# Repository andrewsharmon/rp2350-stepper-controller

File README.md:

# RP2350 coordinated stepper controller

> **Work in progress.** Firmware runs on a Raspberry Pi Pico 2 bench setup.
> The custom board designs are an **unreviewed feasibility first pass**:
> schematics only, no PCB layout, not checked against datasheets or built.
> Don't fabricate them as-is.

A very low-cost, compact controller for up to **10 small stepper motors** (8 mm
micro steppers, 28BYJ-48 converted to bipolar, about 0.2 A per coil or less).
It's aimed at kinetic art first, then lab and robotics use.

There are no stepper-driver ICs. The RP2350 generates sine-PWM microstepping
itself (voltage mode), using PIO state machines fed by DMA, into cheap
DRV8833-class dual H-bridges (AT8833).

## Status

| # | Milestone | State |
|---|---|---|
| 1 | Hardware spec and KiCad schematics for all three boards | first pass, **not reviewed** (open part picks in [hardware/README.md](hardware/README.md)) |
| 2 | One motor: sine PWM via PIO + DMA | done, verified on hardware |
| 3 | 10-axis PWM, ADC monitor, e-stop/button ladder, WS2812 | done on Pico 2; ladder buttons not yet bench-wired |
| 4 | Trajectory generators and profiles, jog modes, telemetry | done (text telemetry; binary framing comes with milestone 5) |
| 5 | Coordinated groups and planner, USB protocol, host tool | done |
| 6 | I²C target, cam/LED shows, flash config, standalone mode | done; I²C target written for the RP2354B board but **untested** (no free pins or I²C master on the bench) |
| 7 | PCB layout, fab, bring-up of the board stack | |

What works today (measured on a Pico 2 + DRV8833 + 8 mm stepper):

- **PWM:** 20 kHz, four-segment H-bridge PWM with slow-decay brake off-time and 1/256-step sine microstepping. Duties below the driver's 0.5 µs minimum pulse are error-diffused.
- **10 axes:** each has its own position, velocity or jog mode on a 1 kHz trajectory tick. Drive amplitude depends on speed, with lower holding current at standstill. Core 1 is about 33-35% loaded, core 0 about 0.5%.
- **Coordinated groups:** up to 4 groups, each owning a set of axes. A group follows a queue of straight lines and arcs in joint space, with every axis starting and finishing together. Lookahead keeps it moving through gentle corners and chord-split arcs, and no axis exceeds its own limits. On the Pico 2, a 300-step-radius circle ran at a constant 800 steps/s and closed exactly.
- **Shows:** keyframe tracks for axes and LED pixels on one timeline, written as JSON, compiled and uploaded to one of 4 flash slots. Axes pass exactly through every keyframe (played as PVT), LED colours fade between keys, and shows can loop. A show is refused if any segment would exceed an axis's speed or acceleration limit. On the Pico 2, a looping 10-axis wave with 9 LED tracks hit all 360 keyframes checked exactly over 2.5 loops.
- **Built-in programs:** 12 looping motion patterns for a row of linear actuators (breathe, travel, standing, ripple, seesaw, zipper, domino, stairs, scan, chase, interference, drift), ±1000 full steps about position 0, all within the default limits (1500 steps/s, 2000 steps/s²). They run along the board's row of connectors, which on single_sh_proto is 5 6 7 8 9 10 1 2 3 4 from the far end to the USB end. They play through the show player as PVT streams, warming up from rest at their first pose. Position 0 is the power-up position, so power up with the actuators mid-stroke (or zero them there with `z`). `prog list`, `prog <n>`, `prog stop` on the console.
- **Standalone mode:** the buttons step through the built-in programs, then the stored shows, with no computer attached. Btn1 clears a latched stop once the e-stop is closed again, or starts / stops the selected entry; Btn2 selects the next one, switching to it if one is playing (the axes stop, then the new one starts). For 1.5 s after a press the axis LEDs show the entry's number as a bar: amber for programs 1-10, cyan for 11-12, magenta for shows. A boot program or show (`boot p<n>` / `boot <n>`, then `save`) starts at power-up.
- **Configuration in flash:** per-axis limits, motion profile, automatic amplitude curve (run low/high, hold, corner speeds) and wiring fixes (reverse direction, swap coils) survive power cycles. Two sectors are written alternately with a generation counter and CRC, so an interrupted save keeps the previous configuration.
- **Streamed PVT:** the host sends position/velocity/time points, and each axis follows a cubic through them. A 10-axis wave streamed at 20 ms per point tracked the ideal curve within 0.0005 steps. Running out of points while moving brakes safely.
- **Telemetry:** up to 1 kHz with selectable axes and fields (position, speed, mode, amplitude, PVT queue, plus motor voltage, ladder, stop state and the last applied command). Each line is numbered so a host can detect drops. Event lines report finished moves, PVT underruns and stops. At 1 kHz with every field on 10 axes, no lines were dropped and core 0 was 39% busy.
- **Electronic cams:** an axis can follow a cam table, so its position is a function of a leader's position: another axis, or one of two virtual leaders with their own speed ramps. Because it's position-based, followers retrace exactly when the leader reverses, at any speed. Cyclic tables can carry a net rise per cycle. Engaging blends in smoothly, and is refused if the follower couldn't keep up at the leader's limits. On the Pico 2, followers matched an independent evaluation of the cam within 0.0013 steps through forward and reverse runs. `save` also stores the loaded cam tables in flash; they are restored at boot.
- **Motion profiles per axis:** `trap`, `scurve` (the default: jerk-limited by a moving average, Tj = 30 ms), `smooth` (two moving averages), `cosine` and `quintic`. Every profile lands exactly on its target within the speed and acceleration limits, and moves can be redirected mid-move without jumps.
- **Safety:** an e-stop or driver fault on the analog ladder cuts all outputs in about 30 µs. A watchdog on core 0 drops outputs to coast if core 1 stalls.
- **Status LEDs:** a WS2812 chain shows overall status plus each axis's speed and direction.

How it works, from trajectory planning to PIO pin toggling: [docs/THEORY.md](docs/THEORY.md).

## Repository layout

```
tools/stepperctl/    host library + command line (binary protocol)
tools/shows/         example shows (JSON; format in tools/stepperctl/show.py)
tools/cams/          example cam tables (JSON: {"cyclic": true, "points": [[x, y], ...]})
tools/pvt_demo.py    host demo: streams a PVT wave over USB serial
tools/web/           browser pages (Web Serial, binary protocol): index.html actuators,
                     tof.html ToF sensor 3D viewer and settings
firmware/            Pico SDK (C) firmware
  third_party/tmf8829/  ams TMF8829 sensor application image (MIT)
  src/               motor PWM (PIO/DMA), microstepping, ADC monitor, ladder, LEDs
  boards/            board header for the custom RP2354B controller
  test/test_host.c   host-side tests (PWM encoder, microstep math, ladder, motion)
  tools/             sine table generator
hardware/            spec, KiCad schematics and BOMs (generated by hardware/gen)
```

## Building the firmware

Requirements:
- [Pico SDK](https://github.com/raspberrypi/pico-sdk) 2.1.1 (set `PICO_SDK_PATH`);
- an `arm-none-eabi` GCC toolchain;
- CMake and Ninja.

```bash
# Custom RP2354B controller (default board)
cmake -S firmware -B firmware/build -G Ninja
cmake --build firmware/build

# single_sh_proto prototype board
cmake -S firmware -B firmware/build-proto -G Ninja -DPICO_BOARD=single_sh_proto
cmake --build firmware/build-proto

# Raspberry Pi Pico 2 bench setup
cmake -S firmware -B firmware/build-pico2 -G Ninja -DPICO_BOARD=pico2
cmake --build firmware/build-pico2
```

Options: `-DNUM_MOTORS=1..10` (default 10), `-DLADDER_BYPASS=ON` (bench without
a ladder wired; never use with motors you can't stop by hand), `-DBOOT_TRACE=ON`.

Flash by copying `stepper.uf2` to the board in BOOTSEL mode, or with picotool:

```bash
picotool load -x firmware/build-pico2/stepper.uf2
```

Host tests (no hardware needed):

```bash
cd firmware/test
cc -std=c11 -O1 -Wall -Wextra -DCONFIG_HOST_TEST -I../src test_host.c ../src/hbridge_encode.c \
   ../src/microstep.c ../src/sine_lut.c ../src/ladder.c ../src/motion.c ../src/group.c \
   ../src/frame.c ../src/config.c ../src/show.c ../src/standalone.c ../src/cam.c ../src/cam_store.c \
   ../src/programs.c ../src/tof_frame.c ../src/tof_map.c -lm -o test_host && ./test_host
```

## ToF sensor (LightRanger 14 Click)

A MikroE LightRanger 14 Click (ams TMF8829 multi-zone dToF, 8x8 to 48x32 zones,
10 mm to 11 m) can hang off the Qwiic port. `tof on` makes I2C1 an I2C host for it
(the I2C target at 0x42 is off meanwhile; `tof off` gives the port back), downloads
the sensor's application into its RAM and loads the 8x8 preset. Driver:
`firmware/src/tmf8829.c`; service and frame streaming: `firmware/src/tof.c`.

Wiring: SDA, SCL, 3V3 and GND from the Qwiic connector. The Click must be set to
I2C, its EN pin (mikroBUS PWM) held high, and it needs 3V3 (bridge JP1
QWIIC_SUPPLY, or power it separately). INT isn't needed: the firmware polls.

`tools/web/tof.html` (Chrome or Edge, opened from file://) connects over USB
serial, switches the sensor on, picks the resolution preset, edits every
register of the configuration page, and draws each measurement as a 3D point
cloud (patches, dots or a surface) and a depth map, with PLY/CSV export. Demo
plays a synthetic scene without a board. From a terminal:

```
tof on            tof res 16         tof period 100     tof start
tof ?             tof get            tof set 0x53 10    tof stop / tof off
```

Not yet run against a real sensor: the register sequences follow ams's reference
driver, and the page was checked with its synthetic frames only.

### ToF map: the sensor drives the actuators

`tof map on` makes the row of linear actuators follow what the sensor sees in a
band across the middle of its field of view (the middle quarter of the rows, the
full width). The band is split left to right into one slice per axis, in the
board's row order (single_sh_proto's connectors run 5 6 7 8 9 10 1 2 3 4 from
the far end to the USB end), and each axis follows the nearest return in its
slice: 150 mm puts it at +1000 full
steps, 300 mm at -1000, and nearer or farther clamps to the ends. A slice with
nothing in it reads as far. Each axis's distance is smoothed (100 ms), and a new
position move goes out when the target changes by 4 steps or more, so the axis's
own limits and profile shape the motion.

Starting switches the sensor on if needed, loads the 16x16 preset, and sets
10 k iterations (the preset's 586 k is for the full range) with a 20 ms period.
Then it measures with no output, unless a host or the console is already
streaming; `tools/web/tof.html` can keep watching. It stops on `tof map off`,
an e-stop, the sensor stopping or failing, a program, show or stress test
starting, or a button starting one. Position 0 is the power-up position, as
for the programs, so power up mid-stroke (or zero there with `z`). The fixed-time
profiles (`cosine`, `quintic`) restart a segment on every retarget; use `scurve`
(the default), `smooth` or `trap`.

```
tof map on            tof map off           tof map ?      (band in zones, live mm and targets)
tof map range 150 300                       tof map steps 1000 -1000    (swap to reverse)
tof map order 1,2,3,4,5,6,7,8,9,10        tof map order board   (axes left to right)
tof map axes 5        tof map mirror on     tof map band 25 100   (height %, width %)
tof map smooth 100    tof map deadband 4    tof map iter 10   tof map period 20   tof map res 16
```

Settings aren't saved to flash yet. On single_sh_proto with the LightRanger 14
and ten actuators it ran at 49 measurements a second (16x16, 10 k iterations,
20 ms), with about 70 of the 256 zones returning; axes under an object at
~210 mm moved to about +150 steps while the rest went to the far end.

## Pico 2 bench setup

| Pico 2 | Connects to |
|---|---|
| GP0-GP3 | motor 1: DRV8833 module AIN1, AIN2, BIN1, BIN2 (motors 2-5 on GP4-GP19) |
| GP20 | WS2812 chain data in (pixel 0 status, pixels 1-10 axes) |
| GP26 | ladder: 10k to 3V3, 20k to GND (idle); see [hardware/README.md](hardware/README.md) |
| GP28 | board ID (optional) |
| VBUS / GND | DRV8833 VM and GND; pull the module's sleep pin (EEP) high |

Motors 6-10 have no pins on the Pico 2, but their state machines and DMA still
run, so the full 10-axis load is exercised.

The USB serial console takes line commands (type `help`). Some examples:

```
m 1 500          move axis 1 to 500 full steps
mr * -100        move every axis back 100 steps
j 3 400          jog axis 3 at 400 steps/s (stops unless repeated within 300 ms)
lim 1 1200 4000  axis 1 limits: 1200 steps/s, 4000 steps/s^2
prof * quintic   minimum-jerk moves on every axis (axes must be at rest)
cam 1 cyclic 0,0 100,40 200,50   cam table 1 (leader x, follower y); +50 per 200-step cycle
vl 1 lim 150 150 virtual leader 1 limits; ce 3 1 v1 makes axis 3 follow cam 1 behind it
vl 1 vel 100     run the virtual leader (negative reverses; followers retrace)
g 1 1,2 800      group 1 = axes 1 and 2, path speed 800 steps/s
gl 1 400 400     group line to (400, 400); ga 1 -300 0 360: full circle around (-300, 0)
p 2 150 300 20   PVT point: axis 2 reaches 150 steps at 300 steps/s, 20 ms after the last
pgo 1,2          start axes 1 and 2 following their queued points on the same tick
t 100            100 telemetry lines/s (header line names the columns)
tf pos,vel,mode  per-axis telemetry fields; ta 1,2 picks axes, ts adds system fields
te on            event lines: E <tick> done <ax> <pos>, underrun, stop, clear
echo off         for scripts: no echo or prompt
drive 1 40 60 25 axis 1 amplitude: 40% at low speed, 60% at high speed, 25% holding
dir 2 rev        reverse axis 2 (coils 2 ba swaps its coils)
cfg / save       show the configuration / write it to flash (axes at rest)
?                status, loads and per-axis table
```

### Host tool (binary protocol)

The same USB port also speaks a framed binary protocol (COBS + CRC-16; the
message spec is [firmware/src/protocol.h](firmware/src/protocol.h)). Frames
and the text console coexist: binary frames are wrapped in 0x00 bytes, which
the console never sends. `tools/stepperctl` is a standard-library Python
client and command line:

```bash
python3 tools/stepperctl ping
python3 tools/stepperctl move 1,2 250 --wait
python3 tools/stepperctl group 1 create 1,2 --feed 800
python3 tools/stepperctl group 1 arc -200 0 360
python3 tools/stepperctl telem --hz 200 --axes 1,2 --seconds 5 > log.csv
python3 tools/stepperctl show upload tools/shows/wave.json --slot 2
python3 tools/stepperctl show run 2          # show list / show stop
python3 tools/stepperctl boot 2 && python3 tools/stepperctl save   # run show 2 at power-up
python3 tools/stepperctl cam load 1 tools/cams/rise_dwell.json
python3 tools/stepperctl cam engage 3 1 v1 && python3 tools/stepperctl vl 1 vel 100
```

```python
from stepperctl import Client          # run from tools/, or put tools/ on sys.path
with Client() as c:
    seq = c.move([1], 500)
    c.wait_settled([1], after=seq)
```

Command-line tool tests (no hardware needed):
`python3 -m unittest discover -s tools/stepperctl -p 'test_*.py' -t tools`

### Browser control page

[tools/web/index.html](tools/web/index.html) drives the actuators from Chrome
or Edge over Web Serial: open the file directly (file:// works) and click
Connect. Each axis gets a position slider (drag to move), hold-to-jog
buttons, →0, Zero and Stop, with live position, speed and amplitude; there
are also an all-axes row, STOP ALL (or Esc), clear stop, manual or automatic
amplitude, speed and acceleration limits, the 12 built-in programs, and the
text console. It speaks the binary protocol on the same USB serial port, so
close any other program that has the port open first.

### I²C (Qwiic) — untested

On the RP2354B board the Qwiic port (I2C1, GPIO 46/47) is an I²C target at
address 0x42 carrying the same requests as the binary protocol, without COBS
framing: write `[type][payload…]`, then read `[n][type][reply payload…]`
(`n` = 0 means not ready yet, read again). See
[firmware/src/i2c_target.h](firmware/src/i2c_target.h). It is compiled out on
the Pico 2 bench build and has not been run on hardware yet.

`tools/pvt_demo.py` streams a travelling wave across every axis as PVT points
(standard-library Python, macOS/Linux):

```bash
tools/pvt_demo.py --amp 200 --hz 0.5 --seconds 15
```

## Notes

- **Sine table:** the SDK's float `sinf` returned wrong values near multiples
  of π/2 on the RP2350, which produced reverse pulses at each coil peak. The
  sine table is generated offline (`firmware/tools/gen_sine_lut.py`), and the
  motion code uses its own polynomials (`firmware/src/trig.h`).
- **Endless DMA:** on the RP2350, endless-mode DMA (`TRANS_COUNT` mode 0xF)
  still needs a non-zero count, or the channel completes immediately.

## License

[MIT](LICENSE), covering both firmware and hardware design files.

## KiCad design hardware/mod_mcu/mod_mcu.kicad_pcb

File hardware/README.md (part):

# Hardware specification

> **Status: unreviewed feasibility first pass.** These schematics, part picks
> and pin maps were put together quickly to check that the concept fits. They
> have not been reviewed, checked against datasheets, laid out or built.
> Expect errors; don't fabricate from them as-is.

Low-cost, compact, up-to-10-axis stepper controller for small high-resistance
steppers (8 mm micro steppers, 28BYJ-48 converted to bipolar, <= 0.2 A/coil).
The MCU generates sine PWM (voltage-mode microstepping) directly into cheap
dual H-bridges; there is no stepper-driver IC.

Prefer LCSC / JLCPCB "basic" parts wherever possible. Part picks marked TBD
are open.

## Stack overview

Three boards, 30 x 30 mm core, joined by fine-pitch board-to-board (BTB)
connectors at opposite edges. No screws: the enclosure captures the stack.

| Tier | Board | Layers | Size |
|---|---|---|---|
| 1 | Controller | 4, 1.0 mm thick | 30 x 30 mm |
| 2 | Universal driver | 2 | 30 x 30 mm |
| 3 | Connector / IO (variant-specific) | 2 | sized by connectors, may overhang |

## Tier 1 - Controller

- MCU: **RP2354B** (QFN-80, 48 GPIO, 2 MB in-package flash). Run the ARM cores (FPU).
- 12 MHz crystal, core-regulator inductor and decoupling per the RP2350 hardware design guide.
  - Crystal: Abracon ABM8-272-T3 (C20625731, 10 pF load, ESR <= 50 ohm). The guide's 15 pF / 1 k values are tuned for it; other crystals need retuning and testing.
  - Inductor: Abracon AOTA-B201610S3R3-101-T has a polarity dot. Lay it out in the same orientation as the Pico 2.
- USB-C receptacle with THT shell legs. The enclosure supports the receptacle so plug forces never reach the BTBs.
- CC1 / CC2: 5.1 k pull-downs, also routed to ADC (GPIO40/41) to read the source current advertisement.
- Power path: `VBUS -> PTC (~1.5 A hold, 1812) -> low-Vf Schottky -> V5_IN -> soft-start switch -> V5 bus -> BTB`.
- 3.3 V LDO (ME6211 class, <= 6 V input) fed from V5_IN, ahead of the switch.
- Soft-start: AO3401A P-FET (C15127) with 100 nF gate-source and 100 k gate-ground (tau 10 ms). At plug-in the cap holds the FET off, then it turns on over a few ms, so the ~70 uF on the V5 bus charges at about 0.1 A. USB sees only the ~11 uF on V5_IN at attach. External 5 V (tier 3) reaches V5_IN through the FET's body diode, then its channel.
- 2x Qwiic (JST-SH 4-pin) on I2C1:
  - The board is not powered from Qwiic. The ME6211 conducts from VOUT back to VIN, so a Qwiic-fed 3V3 would back-power the V5 bus (drivers, LEDs).
  - Solder jumpers for pull-ups (2.2-4.7 k) and for supplying 3V3 to downstream Qwiic devices.
- WS2812-class addressable LED on GPIO45. Its DOUT continues down the stack as LED_DATA.
  - Powered from V5 (needs >= 3.7 V). The 3.3 V data goes through a 74AHCT1G125 on V5 to meet VIH = 0.7 VDD.
- Buttons:
  - BOOTSEL (also readable at runtime), TS-1187A, right edge below connector B. The single boards use the TS-1088-AR02016 instead (same part as Btn1/Btn2).
  - Btn1 and Btn2 on the analog ladder (see below): XUNPU TS-1088-AR02016 (C720477, 3.9 x 3.0 mm, 2 pads), stacked in the top-right corner. They started over the BTB headers for rigidity, but their pads blocked the connector fan-out, so the case should support the board under them.
- SWD test pads.

## Tier 2 - Universal driver

- 10x **AT8833CQ** (Zhongkewei, LCSC C5120769, QFN-16 4 x 4).
  - DRV8833-compatible logic: 00 coast, 01 reverse, 10 forward, 11 brake.
  - VM 2.7-15 V, UVLO <= 2.5 V, 1.0 A RMS. Inputs have 100 k pull-downs.
  - Second source: JSMSEMI DRV8833RTYR / JSM8833RTYR (same QFN-16 4 x 4). Verify its pinout against TI DRV8833RTY before relying on it.
- Passives per chip:
  - AISEN / BISEN: 0.68-1 ohm to ground. Above I = 0.2 V / R (Vtrip 160-240 mV) the chip chops the current in slow decay; it does not report a fault. With 1 ohm that is 0.16-0.24 A. Give it a separate return to the star ground.
  - VCP: 0.1 uF to VM.
  - VINT: 1 uF.
  - These are the AT8833 datasheet values. TI's DRV8833 uses 0.01 uF and 2.2 uF, so don't copy from it.
  - VM: 1-2.2 uF ceramic at the pin.
- Shared bulk: 2-4x 10 uF 0805 spread over the V5 pour.
- nSLEEP: pulled high through 20-75 k (always awake, <= 3.5 mA idle per chip).
- nFAULT (open drain): wire-OR all chips onto the LADDER line.
- VMOTOR is the V5 bus directly.
- VMOTOR_SENSE: 1:5 divider to GPIO42.

AT8833CQ QFN-16 pinout: 1 AISEN, 2 AOUT2, 3 BOUT2, 4 BISEN, 5 BOUT1, 6 nFAULT,
7 BIN1, 8 BIN2, 9 VCP, 10 VM, 11 GND, 12 VINT, 13 AIN2, 14 AIN1, 15 nSLEEP,
16 AOUT1, plus the exposed pad to GND.

## Tier 3 - Connector / IO

- Motor connectors per variant. Each uses the motor's stock plug:
  - `io_xh`, 28BYJ-48: one JST-XH 5-pin (B5B-XH-A, C157991) per motor, ten total.
    - Pins: 1 blue, 2 pink, 3 yellow, 4 orange. Pin 5 (red centre tap) is not connected after the bipolar mod.
    - Coils: A = pins 1/3, B = pins 2/4.
  - `io_sh`, dual 8 mm micro steppers: one JST-SH 8-pin (BM08B-SRSS-TB, C160394) per motor pair, five total.
    - Pins 1-4 = first motor (A1 A2 B1 B2), pins 5-8 = second motor.
  - Firmware remaps coil order and polarity per axis, so lead-colour variations can be fixed in software.
- Optional external 5 V input -> Schottky -> V5 bus. This powers everything without USB.
- LED strip output (V5 / DATA / GND):
  - Data: 74AHCT1G125 buffer (powered from V5), then a 33-100 ohm series resistor.
  - Strip power, chosen by footprint: shared V5 through a polyfuse, or a separate LED power input.
- E-stop jack and panel buttons, in parallel with the ladder.
- Board ID: one resistor to GND, read through the controller pull-up on GPIO43. See the board-ID table below.

## Interconnect (BTB)

- **Part:** Hirose DF40, 0.4 mm pitch, 40 pins, **2.0 mm stack height**:
  - **Header** DF40C-40DP-0.4V(51) (C424643). Goes on the **underside of the upper board**. The header is the same for every DF40 stack height.
  - **Socket** DF40C(2.0)-40DS-0.4V(51) (C597934). Goes on the **top of the lower board**. The socket sets the stack height.
  - Rated 0.3 A per contact. The four corner contacts (pins 1, 2, 39, 40) are metal fittings per Hirose (catalogue note 3): they are soldered for strength but left unconnected, leaving 36 usable pins.
  - The 2.0 mm stack leaves room between boards for low parts (0402 passives, QFNs, SOT-23) on the facing sides. Keep anything taller than ~1 mm off them, and don't put a part opposite another one on the facing board if the two heights add up to more than ~1.7 mm.
- **Footprints** are in `lib/stack.pretty`, generated by `gen/footprints.py` from the DF40 catalogue's recommended layouts:
  - Socket: 0.20 x 0.70 pads (rows 2.38-3.78 mm across), plus the 1.5 mm layout-prohibited strip between the rows as a copper keepout.
  - Header: 0.23 x 0.66 pads (rows 2.05-3.37 mm across), plus 0.35 mm metal-fitting tabs 0.30-0.65 mm beyond each row end.
  - Pin 1 at -X. The socket's odd row is at -Y; the header's is drawn at +Y, so after the flip onto the underside header pin n sits over socket pin n. Still check it in the 3D viewer before ordering.
- **Not polarized** (Hirose note 5). Two connectors per interface at offset positions key the stack so the boards only mate one way: A is 2 mm below the board centre line, B on it.
- BTB pins carry roughly 0.3-0.5 A each.
- The authoritative pin lists are `btb_a()` and `btb_b()` in `gen/build.py`.

| Connector | Controller <-> driver | Driver <-> tier 3 |
|---|---|---|
| A | motors 1-7 inputs (28), 4x V5, 3x GND, 3V3, 4 corner NC | motors 1-7 outputs (28), 4x V5, 4x GND, 4 corner NC |
| B | motors 8-10 inputs (12), LED_DATA, LADDER, BOARD_ID, VMOT_SENSE, 9x V5, 11x GND, 4 corner NC | motors 8-10 outputs (12), LED_DATA, LADDER, BOARD_ID, 9x V5, 12x GND, 4 corner NC |

Pin order follows the MCU's pin order, so the controller's traces fan in without crossing. Connectors are placed pin 1 at the top: A down the left edge (power, then M1 from the MCU's top-left corner, M2-M5 down its left side, M6-M7 round its bottom-left), B down the right edge (utilities, then M10, M9, M8). M6/M7 are on A so they don't cross the crystal and SWD pins on the MCU's bottom side. The driver board shares V5 between both connectors, so the uneven V5 split doesn't matter. The driver's sockets copy the controller headers' positions and rotation.

**Board ID:** the 10 k 1% pull-up to 3V3 is on the controller. Each tier-3 variant fits one resistor to GND, 5% is fine. With no tier 3 attached, the line reads 3.3 V.

The values are common 0402 parts. Ranges are worst case for a 5% ID resistor and the 1% pull-up; adjacent levels stay at least 249 mV apart, and the thresholds sit midway between ranges.

| ID resistor | Nominal | Range (mV) | Threshold above (mV) | Board |
|---|---|---|---|---|
| 0 ohm | 0 mV | 0 | 150 | |
| 1 k | 300 mV | 284-316 | 440 | |
| 2.2 k | 595 mV | 566-624 | 820 | |
| 4.7 k | 1055 mV | 1012-1098 | 1350 | io_sh (dual 8 mm micro steppers) |
| 10 k | 1650 mV | 1599-1699 | 1960 | io_xh (28BYJ-48) |
| 22 k | 2269 mV | 2225-2310 | 2500 | |
| 47 k | 2721 mV | 2691-2749 | 3020 | |
| not fitted | 3300 mV | 3300 | - | no tier 3 attached |

## GPIO map (RP2354B)

| GPIO | Function |
|---|---|
| 0-39 | Motor n (1-10) on GPIO 4(n-1)..4(n-1)+3 = AIN1 AIN2 BIN1 BIN2 |
| 40 | USB-C CC1 (ADC0) |
| 41 | USB-C CC2 (ADC1) |
| 42 | VMOTOR_SENSE, 1:5 (ADC2). Can't tell external power from USB (both feed V5 through Schottkys) |
| 43 | Tier-3 board ID (ADC3) |
| 44 | Ladder (ADC4) |
| 45 | WS2812 data |
| 46 | Qwiic SDA (I2C1) |
| 47 | Qwiic SCL (I2C1) |

PIO allocation:

| PIO block | State machines | Use |
|---|---|---|
| PIO0 | SM0-3 | Motors 1-4 |
| PIO1 | SM0-3 | Motors 5-8 |
| PIO2 (GPIOBASE = 16) | SM0-1 | Motors 9-10 |
| PIO2 | SM2 | WS2812 |
| PIO2 | SM3 | Spare |

Use external pull-ups on all inputs on A2 silicon (RP2350-E9 erratum; fixed from A3).

## Ladder on GPIO44

```
3V3 --[10k]--+---------> GPIO44 (ADC4), 100 nF to GND
             |-- E-stop (NC) --[20k]-- GND   (solder jumper bypass when no e-stop)
             |-- Btn1 ---------[10k]-- GND
             |-- Btn2 ---------[3.3k]- GND
             '-- nFAULT (open drain, all drivers)
```

| Condition | Voltage | Meaning |
|---|---|---|
| E-stop open or cable cut | 3.3 V | STOP |
| Idle | ~2.2 V | normal |
| Btn1 | ~1.3 V | user 1 |
| Btn2 | ~0.7 V | user 2 |
| nFAULT | ~0 V | driver fault, STOP |

Use 1% resistors. Thresholds sit midway between the levels; debounce over 2-3 samples.

A held button hides an open e-stop (e-stop open + Btn1 = 1.65 V, + Btn2 = 0.82 V). Firmware latches a stop on 1.49-1.76 V held 5 ms, or on any button held over 3 s; see `firmware/src/ladder.h`.

## Electrical notes

- PWM frequency is about 20 kHz. The AT8833 input deglitch (about 450 ns) sets a minimum pulse of about 0.5 us, roughly 1% duty. Firmware dithers duties below that.
- Wait about 100 ms after power-up before energizing motors (V5 soft-start settling).
- USB budget comes from CC; brownout guard from VMOTOR_SENSE.
- RP2350-E9 (a GPIO with its input buffer on can sit near 2.2 V, which the AT8833's >= 2 V VIH reads as high) needs no hardware fix on the motor inputs. It is fixed in silicon from A3 (A4 is the production stepping; order A4). On A2 it can't occur after a power-on or RUN reset (input enable starts clear), and the firmware turns the motor pins' input buffers off (they are never read), so they stay off across a watchdog reset whether or not it resets the pads. The AT8833's 100 k pull-downs are enough.
- Tier 3: the NO_ESTOP jumper ships bridged. It must be cut when an e-stop is fitted, or the e-stop does nothing. Mark this on the silkscreen.

## Single board (`single_sh`)

Controller, driver and the `io_sh` connectors on one PCB, from the `single_sh/` schematic (`single()` in `gen/build.py`). Fully routed: 0 unconnected, no DRC errors, schematic parity clean.

- Schematic: a wired, hierarchical drawing (`gen/single_sh_sch.py`), unlike the label-only stack schematics.
  - Sheets: overview, power and USB, MCU, motor drivers, connectors and UI. Each block is framed, with design notes on its sheet.
  - Inter-sheet signals (motor lines, LADDER, BOARD_ID, I2C, CC, USB) are global labels. Power rails are power symbols, so their PCB nets are `GND`, `+3V3`, `V5` and so on; nets local to a sheet are named `/<sheet>/<label>`, e.g. `/Power/V5_IN`.
  - The AT8833 uses a project symbol (`lib/stack.kicad_sym`, written by `build.py`) with the DRV8833RTY pin numbers, laid out for the drawing; VINT is typed as an output, so it needs no PWR_FLAG.

- **122 x 20 mm**, 4 layers, 1.6 mm thick. All parts on top; only the THT legs of the USB-C and the JST-PH/XH connectors come through.
- Layers: F.Cu parts and signals, In1 solid GND, In2 V5, B.Cu signals. In2 has a 3V3 island under the MCU, joined to the LDO by a thin finger along the -y edge.
- Along the board: USB-C (mouth on the short edge) and power path | drivers M4 M3 M2 M1 | MCU | drivers M10 M9 M8 M7 M6 M5 | LED strip connector.
  - Motor connectors run along one long edge in the order J12 J11 | J15 J14 J13, so each motor bus leaves the MCU in pin order and never crosses itself.
  - Qwiic x2, BOOTSEL, e-stop, panel buttons, 5 V in, status LED and LED power run along the other long edge, above the drivers.
- Driver cell: AT8833 rotated so its outputs face the connector. VINT/VM/VCP caps sit above it; the 0603 sense resistors sit below, ISEN pads inboard, each GND pad with its own via (R16 and R20 instead tie to the neighbouring cell's GND pad).
  - BOUT2 runs down between the two ISEN pads and BOUT1 under R_B's body. The resistors went 0805 -> 0603 in place on the routed board: pad 1 (ISEN) kept, GND pad 0.275 mm inboard (R5 and R11 keep the GND pad instead, clear of a neighbouring via and track).
  - The connector's pin order (B2 B1 A2 A1, left to right) runs against the driver's (A1 A2 B2 B1), so A1/A2 hop over B1/B2 on short In2 jumpers (4 vias per motor).
  - Swapping this board's connector pin assignment (pins 1-2 = coil B, pins 3-4 = coil A reversed) would remove the jumpers, if firmware maps coil order and polarity per board. Not done, because the cable pinout would then differ from `io_sh`.
- V5 enters the In2 plane through via clusters at the soft-start FET, the external 5 V diode and the LED-strip fuse.
- Layout source: `single_sh()` in `gen/pcbgen.py` (placement and zones).
  - The driver cells and the core regulator were pre-routed by script. The rest was routed with Freerouting 2.5.0 plus a small grid router.
  - Those routing scripts are not in the repo; the board is hand-edited from here.
- Silkscreen: reference designators are hidden (too dense).
  - Motor numbers sit above each connector; function labels are on top where they fit, otherwise on the underside.
  - The underside also carries the NO_ESTOP cut warning.
  - The 4 remaining silkscreen warnings are outlines touching each other or the board edge.

### Fabrication (JLCPCB)

`gen/jlcfab.py` writes the order files to `single_sh/jlcpcb/`: Gerbers + Excellon drill (zipped), the BOM and the placement (CPL) file. Run it with KiCad's Python; `--check` also verifies the placements.

```bash
/Applications/KiCad/KiCad.app/Contents/Frameworks/Python.framework/Versions/Current/bin/python3 gen/jlcfab.py single_sh --check
```

- JLCPCB places each part with its own library footprint, so `CPL_FIX` corrects rotation and origin per LCSC part (SOT-23, SOT-23-5, WS2812, the JST connectors and USB-C need it).
  - `--check` fetches those footprints from the JLCEDA library and compares their pads with the KiCad pads.
  - All 142 placements land within 0.003 mm of centre with every pin on its own pad.
- Pin numbering traps:
  - SS54 (C22452): JLCPCB numbers 1 = anode, 2 = cathode, the reverse of KiCad's diodes. `PAD_MAP` handles it; the diodes need no extra rotation.
  - AOTA inductor (L1): the dot goes at the +1V1 end, as on the Pico 2 (RP2350 datasheet, regulator layout figure). JLCPCB's silkscreen and Abracon's top view put the dot at their pad 2, so pad 2 lands on +1V1. JLCPCB's placement preview shows the dot there; the order remark repeats it.
- The BOM has one line per LCSC part. JLCPCB unticks a part that appears on several lines.
- First order (2026-10-07, 10 boards, $314 before shipping):
  - PCB: 4 layers, 1.6 mm, ENIG (0.4 mm pitch QFN-80), min via 0.15/0.3 mm, plugged vias.
  - Assembly: Standard PCBA, top side, confirm parts placement with no auto-confirm.
- Cost drivers:
  - The 0.15 mm via option ($37) forces a 4-wire Kelvin test ($18) and TG155.
  - The WS2812B-2020 (D2) is Standard-PCBA only, as are its alternatives. Standard adds $25 setup, feeder fees and 5 mm edge rails (a 122 x 70 mm panel, nearly double the shipping weight). Economic with D2 left off was $265.
  - THT parts (JST PH/XH, the USB-C shell legs) are hand soldered, about $6.
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
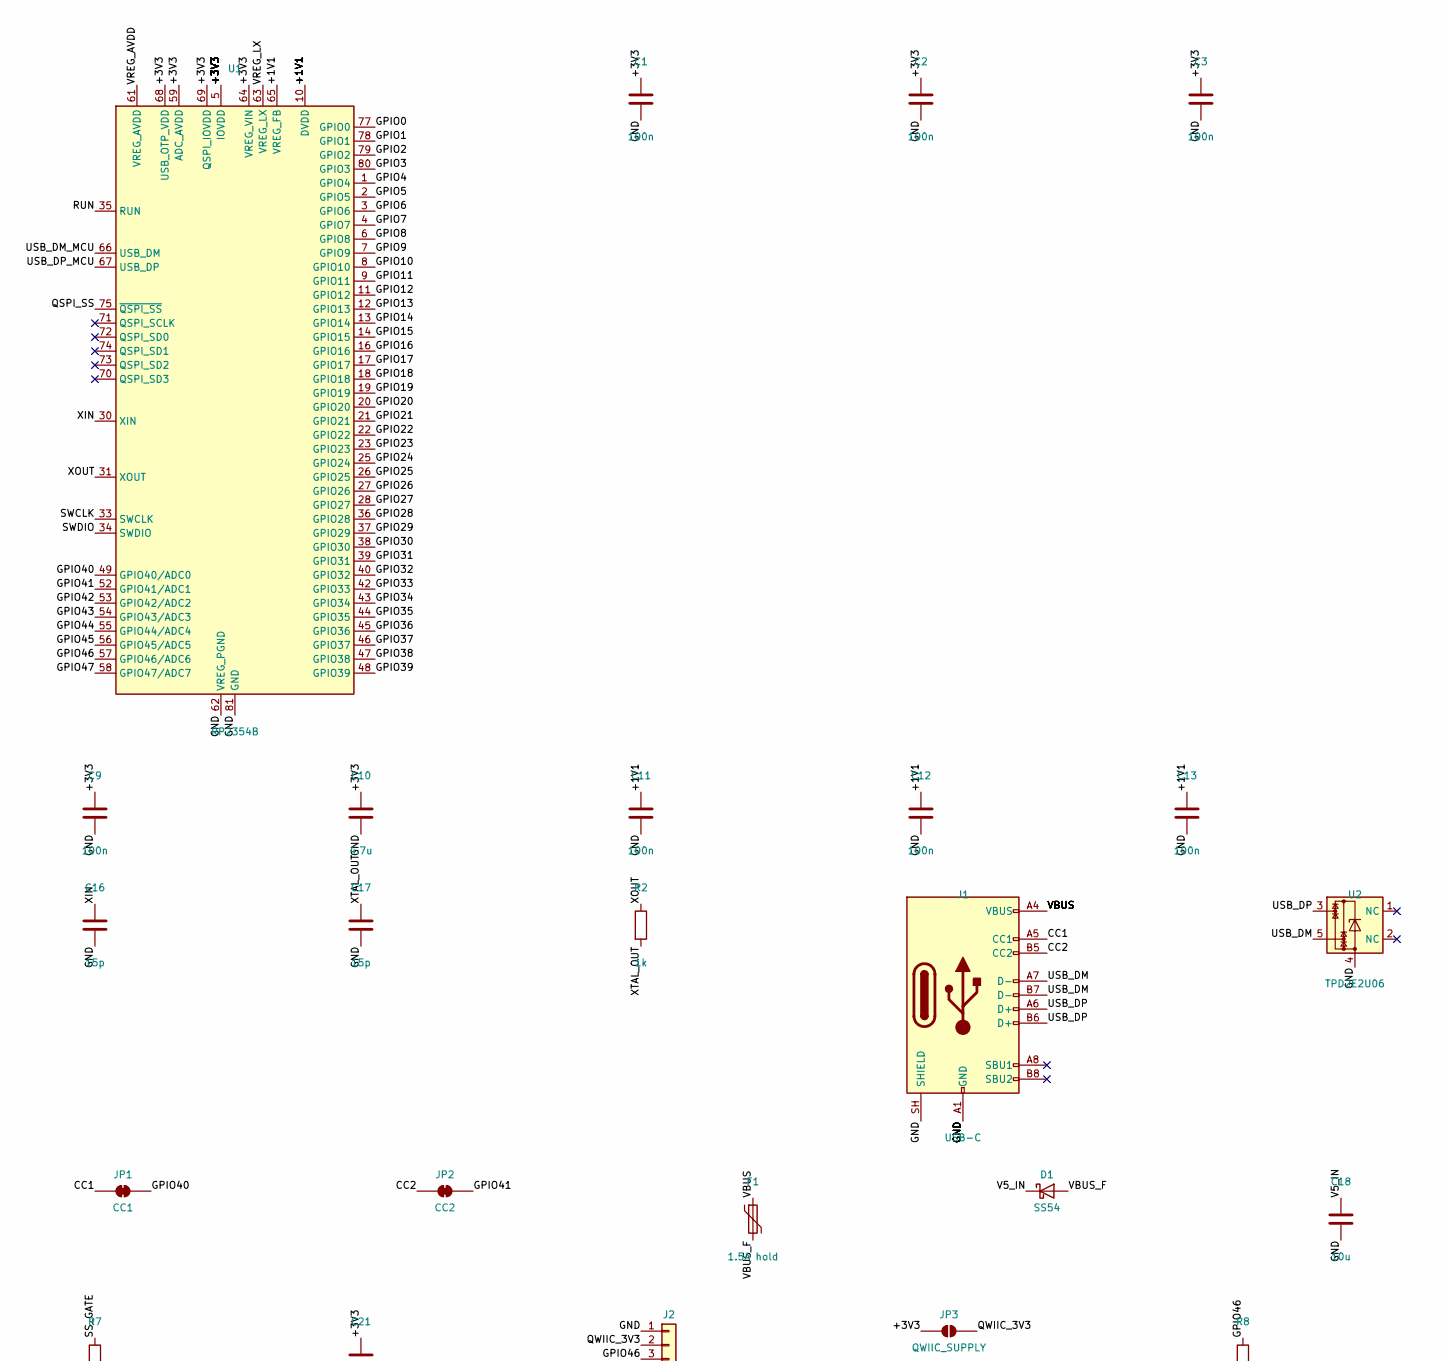
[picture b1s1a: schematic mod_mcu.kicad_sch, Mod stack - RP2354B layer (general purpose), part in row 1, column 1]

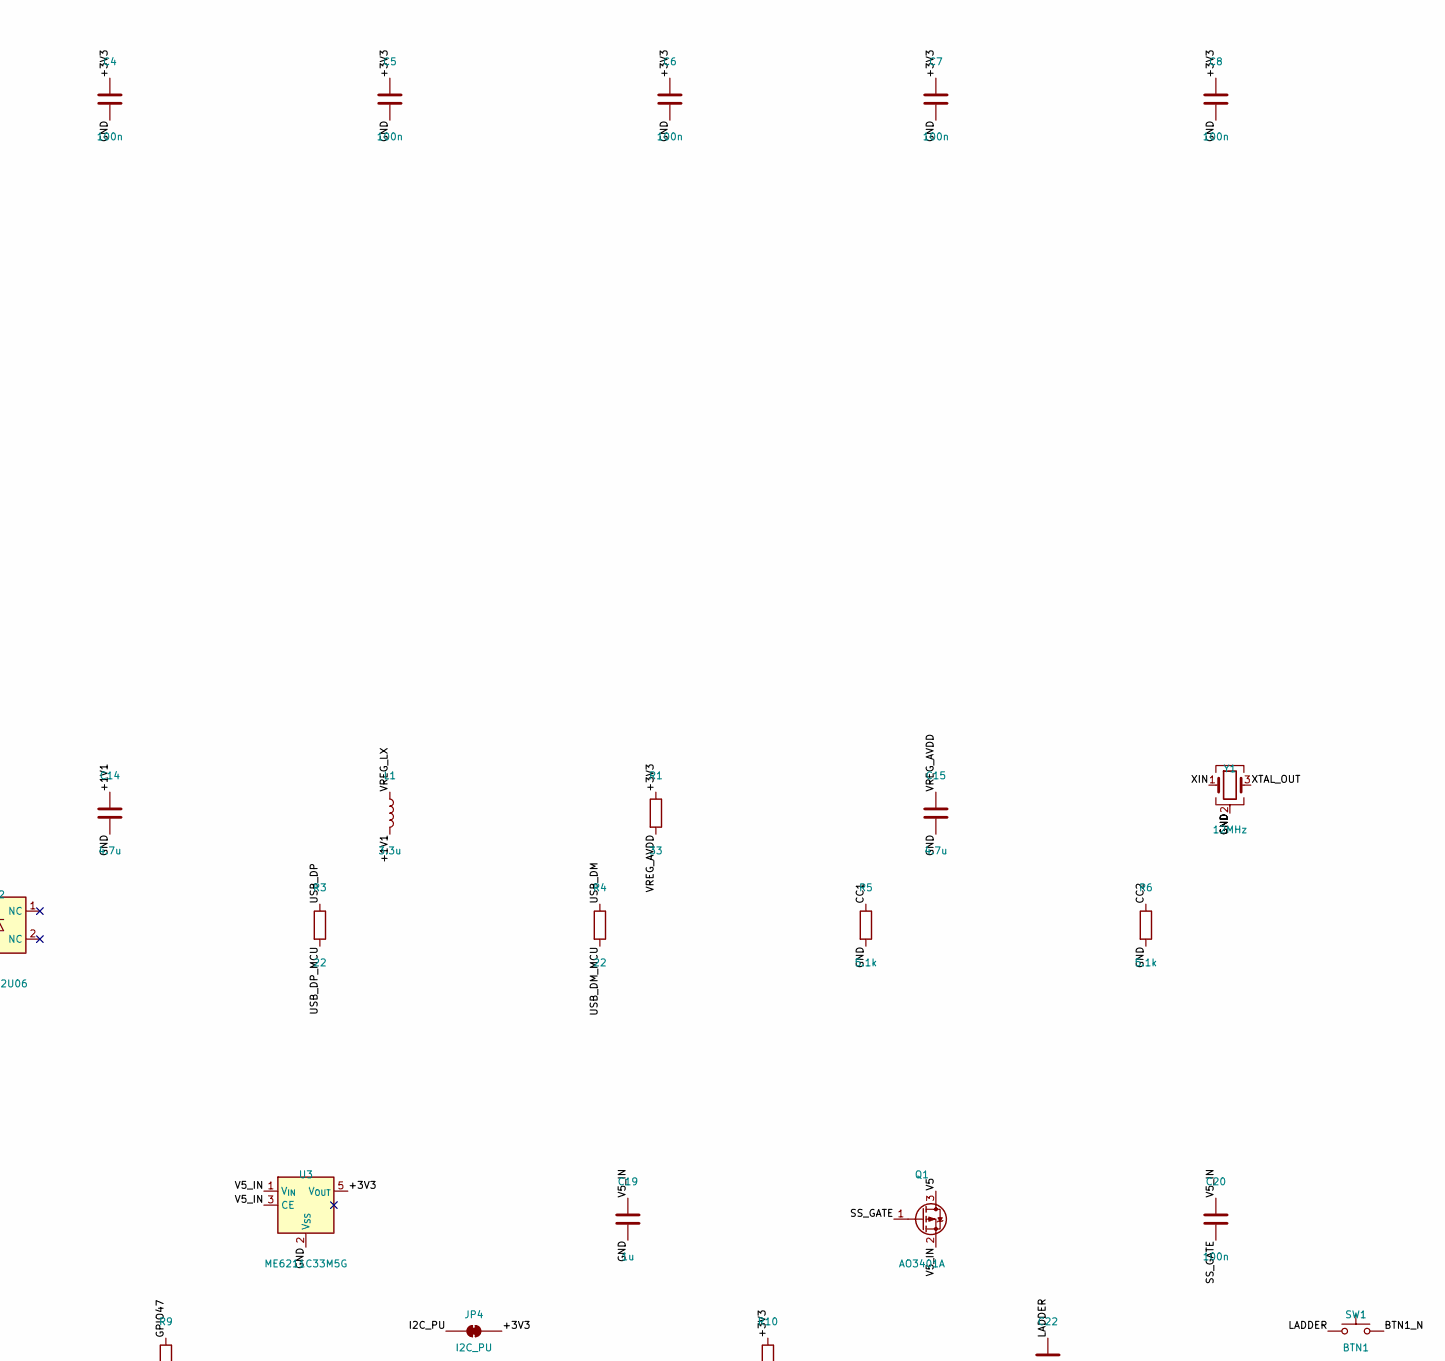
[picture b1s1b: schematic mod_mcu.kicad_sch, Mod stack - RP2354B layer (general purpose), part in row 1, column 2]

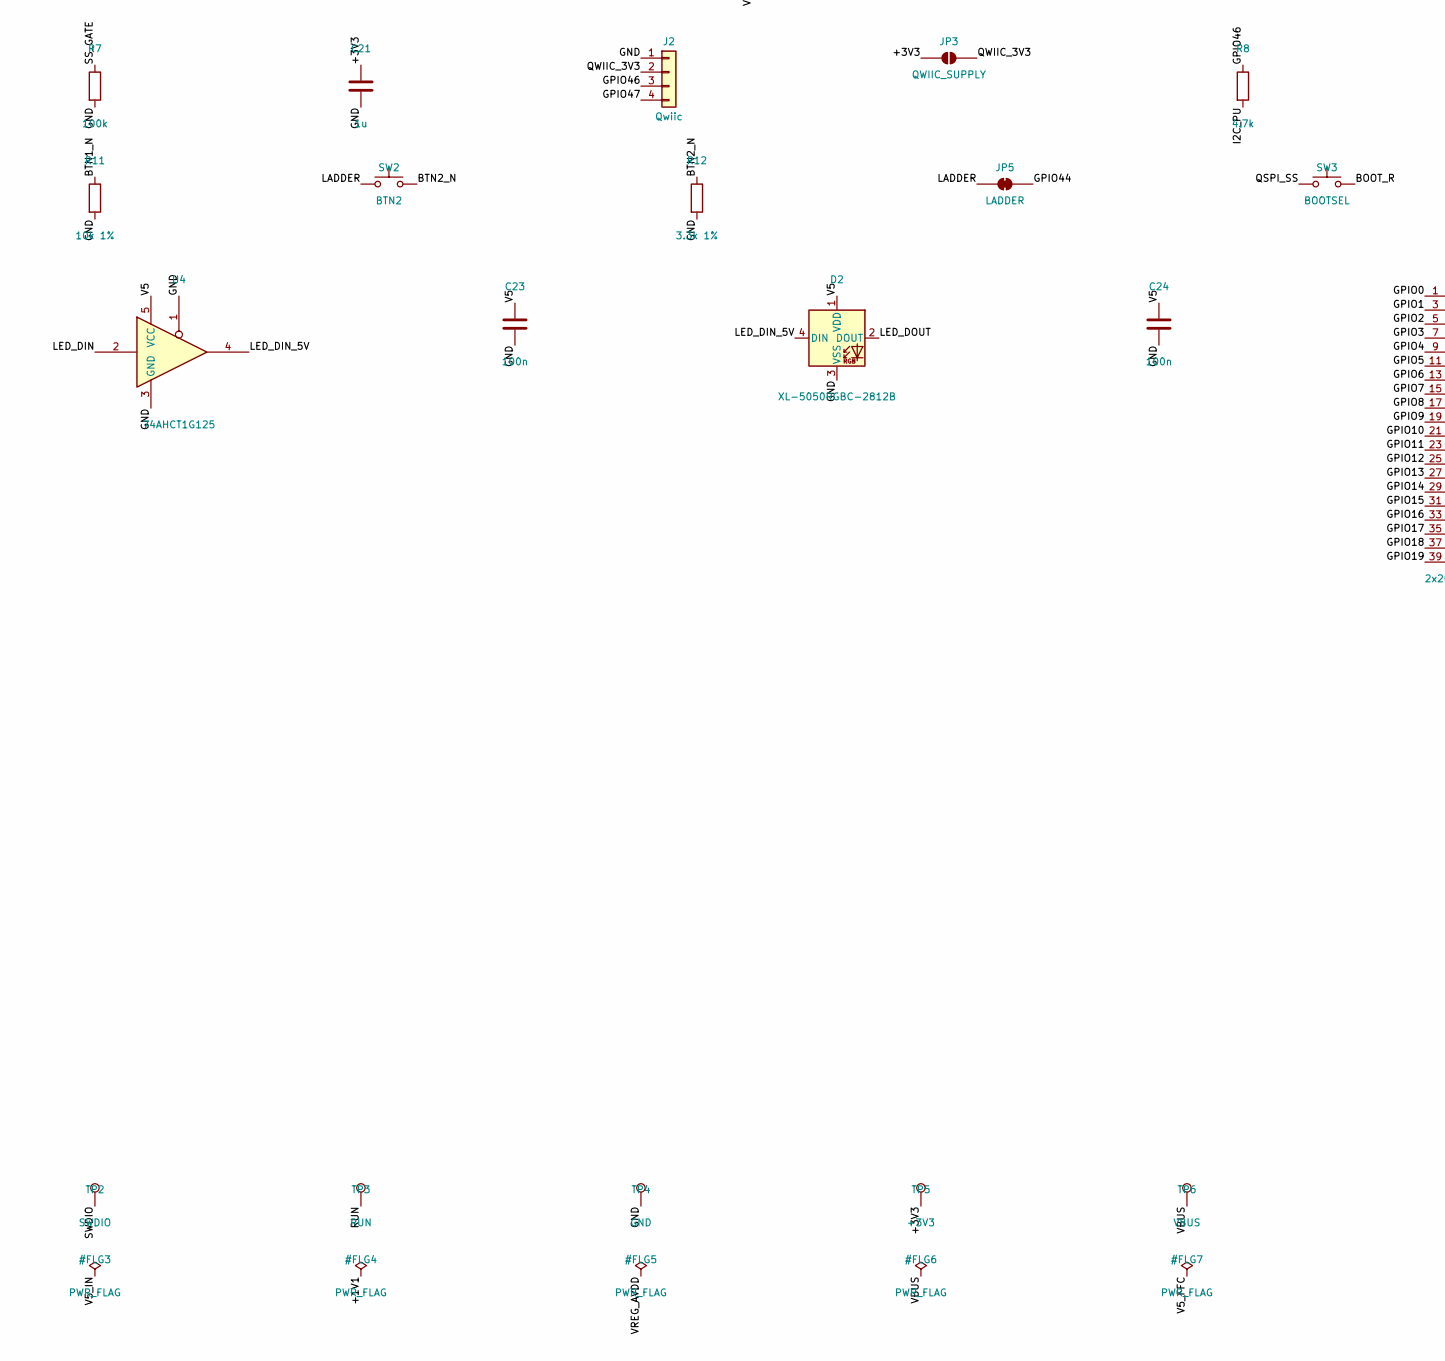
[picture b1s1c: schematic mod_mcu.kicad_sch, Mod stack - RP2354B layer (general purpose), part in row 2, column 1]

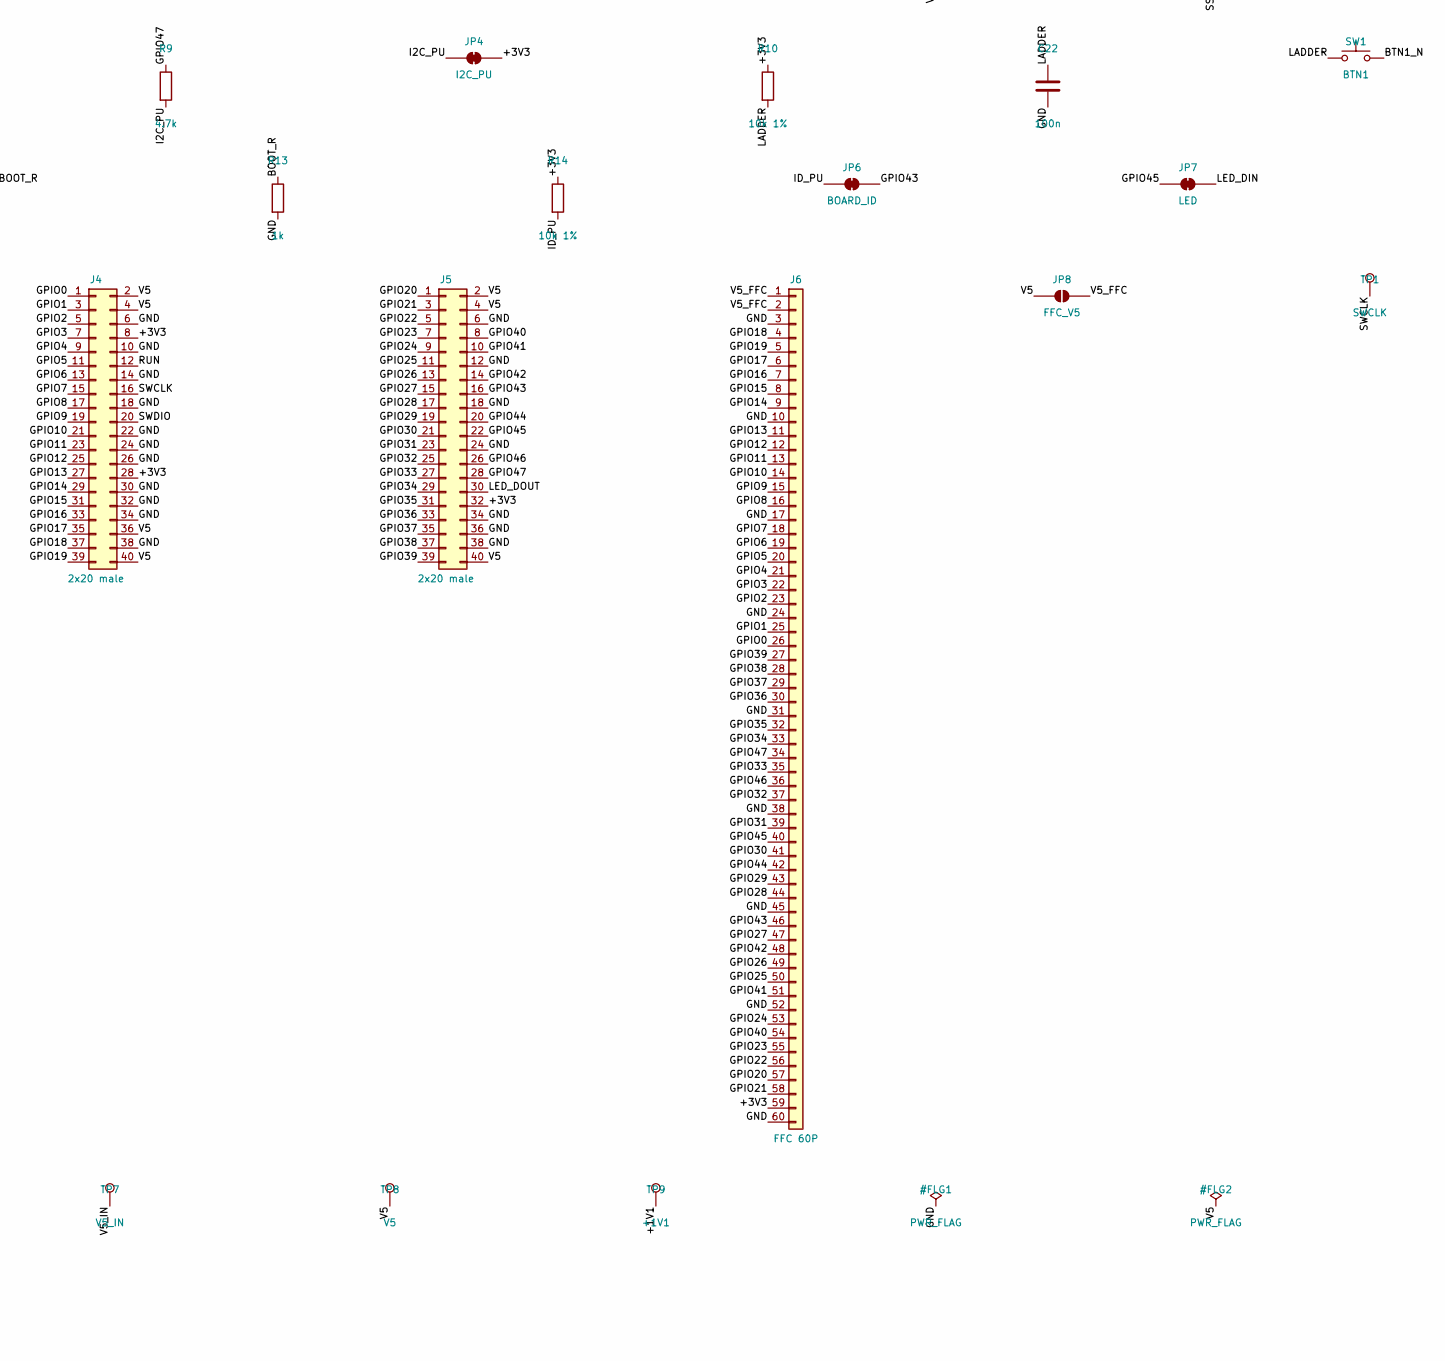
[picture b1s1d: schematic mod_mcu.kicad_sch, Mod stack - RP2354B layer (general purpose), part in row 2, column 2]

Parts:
C1, C2, C3, C4, C5, C6, C7, C8, C9, C11, C12, C13, C20, C22, C23, C24: 100n; C_0402_1005Metric; MPN CL05B104KO5NNNC; LCSC C1525
C10, C14, C15: 4.7u; C_0402_1005Metric; MPN CL05A475MP5NRNC; LCSC C23733
C16, C17: 15p; C_0402_1005Metric; MPN 0402CG150J500NT; LCSC C1548
C18: 10u; C_0603_1608Metric; MPN CL10A106KP8NNNC; LCSC C19702
C19, C21: 1u; C_0402_1005Metric; MPN CL05A105KA5NQNC; LCSC C52923
D1: SS54; D_SMA; MPN SS54; LCSC C22452
D2: XL-5050RGBC-2812B; LED_WS2812B_PLCC4_5.0x5.0mm_P3.2mm; MPN XL-5050RGBC-2812B; LCSC C2843785
F1: 1.5A hold; Fuse_1206_3216Metric; MPN SMD1206B150TFT; LCSC C269120
J1: USB-C; USB_C_Receptacle_HRO_TYPE-C-31-M-12; MPN TYPE-C-31-M-12; LCSC C165948
J2: Qwiic; JST_SH_BM04B-SRSS-TB_1x04-1MP_P1.00mm_Vertical; MPN BM04B-SRSS-TB; LCSC C160390
J4, J5: 2x20 male; PinHeader_2x20_P2.54mm_Vertical; MPN PZ254-2-20-Z-8.5; LCSC C3012260
J6: FFC 60P; FFC_0.5mm_60P_FlipTop; MPN 05A20L60P; LCSC C22435645
JP1: CC1; SolderJumper-2_P1.3mm_Bridged_RoundedPad1.0x1.5mm
JP2: CC2; SolderJumper-2_P1.3mm_Bridged_RoundedPad1.0x1.5mm
JP3: QWIIC_SUPPLY; SolderJumper-2_P1.3mm_Open_RoundedPad1.0x1.5mm
JP4: I2C_PU; SolderJumper-2_P1.3mm_Bridged_RoundedPad1.0x1.5mm
JP5: LADDER; SolderJumper-2_P1.3mm_Bridged_RoundedPad1.0x1.5mm
JP6: BOARD_ID; SolderJumper-2_P1.3mm_Bridged_RoundedPad1.0x1.5mm
JP7: LED; SolderJumper-2_P1.3mm_Bridged_RoundedPad1.0x1.5mm
JP8: FFC_V5; SolderJumper-2_P1.3mm_Open_RoundedPad1.0x1.5mm
L1: 3.3u; L_Cenker_CKCS201610; MPN AOTA-B201610S3R3-101-T; LCSC C42411119
Q1: AO3401A; SOT-23; MPN AO3401A; LCSC C15127
R1: 33; R_0402_1005Metric; MPN 0402WGF330JTCE; LCSC C25105
R2, R13: 1k; R_0402_1005Metric; MPN 0402WGF1001TCE; LCSC C11702
R3, R4: 22; R_0402_1005Metric; MPN 0402WGF220JTCE; LCSC C25092
R5, R6: 5.1k; R_0402_1005Metric; MPN 0402WGF5101TCE; LCSC C25905
R7: 100k; R_0402_1005Metric; MPN 0402WGF1003TCE; LCSC C25741
R8, R9: 4.7k; R_0402_1005Metric; MPN 0402WGF4701TCE; LCSC C25900
R10, R11, R14: 10k 1%; R_0402_1005Metric; MPN 0402WGF1002TCE; LCSC C25744
R12: 3.3k 1%; R_0402_1005Metric; MPN 0402WGF3301TCE; LCSC C25890
SW1: BTN1; SW_SPST_TS-1088-xR020; MPN TS-1088-AR02016; LCSC C720477
SW2: BTN2; SW_SPST_TS-1088-xR020; MPN TS-1088-AR02016; LCSC C720477
SW3: BOOTSEL; SW_SPST_TS-1088-xR020; MPN TS-1088-AR02016; LCSC C720477
TP1: SWCLK; TestPoint_Pad_D1.0mm
TP2: SWDIO; TestPoint_Pad_D1.0mm
TP3: RUN; TestPoint_Pad_D1.0mm
TP4: GND; TestPoint_Pad_D1.0mm
TP5: +3V3; TestPoint_Pad_D1.0mm
TP6: VBUS; TestPoint_Pad_D1.0mm
TP7: V5_IN; TestPoint_Pad_D1.0mm
TP8: V5; TestPoint_Pad_D1.0mm
TP9: +1V1; TestPoint_Pad_D1.0mm
U1: RP2354B; QFN-80-1EP_10x10mm_P0.4mm_EP3.4x3.4mm; MPN RP2354B; LCSC C39843328
U2: TPD2E2U06; SOT-553; MPN TPD2E2U06DRLR; LCSC C1972959
U3: ME6211C33M5G; SOT-23-5; MPN ME6211C33M5G-N; LCSC C82942
U4: 74AHCT1G125; SOT-23-5; MPN SN74AHCT1G125DBVR; LCSC C7484
Y1: 12MHz; Crystal_SMD_3225-4Pin_3.2x2.5mm; MPN ABM8-272-T3; LCSC C20625731

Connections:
/+1V1: C11.1, C12.1, C13.1, C14.1, L1.2, TP9.1, U1.10 (DVDD), U1.32 (DVDD), U1.51 (DVDD), U1.65 (VREG_FB)
/+3V3: C1.1, C2.1, C3.1, C4.1, C5.1, C6.1, C7.1, C8.1, C9.1, C10.1, C21.1, J4.8, J4.28, J5.32, J6.59, JP3.1 (A), JP4.2 (B), R1.1, R10.1, R14.1, TP5.1, U1.5 (IOVDD), U1.15 (IOVDD), U1.24 (IOVDD), U1.29 (IOVDD), U1.41 (IOVDD), U1.50 (IOVDD), U1.59 (ADC_AVDD), U1.60 (IOVDD), U1.64 (VREG_VIN), U1.68 (USB_OTP_VDD), U1.69 (QSPI_IOVDD), U1.76 (IOVDD), U3.5 (V_{OUT})
/BOOT_R: R13.1, SW3.2
/BTN1_N: R11.1, SW1.2
/BTN2_N: R12.1, SW2.2
/CC1: J1.A5 (CC1), JP1.1 (A), R5.1
/CC2: J1.B5 (CC2), JP2.1 (A), R6.1
/GND: C1.2, C2.2, C3.2, C4.2, C5.2, C6.2, C7.2, C8.2, C9.2, C10.2, C11.2, C12.2, C13.2, C14.2, C15.2, C16.2, C17.2, C18.2, C19.2, C21.2, C22.2, C23.2, C24.2, D2.3 (VSS), J1.A1 (GND), J1.A12 (GND), J1.B1 (GND), J1.B12 (GND), J1.SH (SHIELD), J2.1, J4.6, J4.10, J4.14, J4.18, J4.22, J4.24, J4.26, J4.30, J4.32, J4.34, J4.38, J5.6, J5.12, J5.18, J5.24, J5.34, J5.36, J5.38, J6.3, J6.10, J6.17, J6.24, J6.31, J6.38, J6.45, J6.52, J6.60, R5.2, R6.2, R7.2, R11.2, R12.2, R13.2, TP4.1, U1.62 (VREG_PGND), U1.81 (GND), U2.4, U3.2 (V_{SS}), U4.1, U4.3 (GND), Y1.2 (G), Y1.4 (G)
/GPIO0: J4.1, J6.26, U1.77 (GPIO0)
/GPIO1: J4.3, J6.25, U1.78 (GPIO1)
/GPIO2: J4.5, J6.23, U1.79 (GPIO2)
/GPIO3: J4.7, J6.22, U1.80 (GPIO3)
/GPIO4: J4.9, J6.21, U1.1 (GPIO4)
/GPIO5: J4.11, J6.20, U1.2 (GPIO5)
/GPIO6: J4.13, J6.19, U1.3 (GPIO6)
/GPIO7: J4.15, J6.18, U1.4 (GPIO7)
/GPIO8: J4.17, J6.16, U1.6 (GPIO8)
/GPIO9: J4.19, J6.15, U1.7 (GPIO9)
/GPIO10: J4.21, J6.14, U1.8 (GPIO10)
/GPIO11: J4.23, J6.13, U1.9 (GPIO11)
/GPIO12: J4.25, J6.12, U1.11 (GPIO12)
/GPIO13: J4.27, J6.11, U1.12 (GPIO13)
/GPIO14: J4.29, J6.9, U1.13 (GPIO14)
/GPIO15: J4.31, J6.8, U1.14 (GPIO15)
/GPIO16: J4.33, J6.7, U1.16 (GPIO16)
/GPIO17: J4.35, J6.6, U1.17 (GPIO17)
/GPIO18: J4.37, J6.4, U1.18 (GPIO18)
/GPIO19: J4.39, J6.5, U1.19 (GPIO19)
/GPIO20: J5.1, J6.57, U1.20 (GPIO20)
/GPIO21: J5.3, J6.58, U1.21 (GPIO21)
/GPIO22: J5.5, J6.56, U1.22 (GPIO22)
/GPIO23: J5.7, J6.55, U1.23 (GPIO23)
/GPIO24: J5.9, J6.53, U1.25 (GPIO24)
/GPIO25: J5.11, J6.50, U1.26 (GPIO25)
/GPIO26: J5.13, J6.49, U1.27 (GPIO26)
/GPIO27: J5.15, J6.47, U1.28 (GPIO27)
/GPIO28: J5.17, J6.44, U1.36 (GPIO28)
/GPIO29: J5.19, J6.43, U1.37 (GPIO29)
/GPIO30: J5.21, J6.41, U1.38 (GPIO30)
/GPIO31: J5.23, J6.39, U1.39 (GPIO31)
/GPIO32: J5.25, J6.37, U1.40 (GPIO32)
/GPIO33: J5.27, J6.35, U1.42 (GPIO33)
/GPIO34: J5.29, J6.33, U1.43 (GPIO34)
/GPIO35: J5.31, J6.32, U1.44 (GPIO35)
/GPIO36: J5.33, J6.30, U1.45 (GPIO36)
/GPIO37: J5.35, J6.29, U1.46 (GPIO37)
/GPIO38: J5.37, J6.28, U1.47 (GPIO38)
/GPIO39: J5.39, J6.27, U1.48 (GPIO39)
/GPIO40: J5.8, J6.54, JP1.2 (B), U1.49 (GPIO40/ADC0)
/GPIO41: J5.10, J6.51, JP2.2 (B), U1.52 (GPIO41/ADC1)
/GPIO42: J5.14, J6.48, U1.53 (GPIO42/ADC2)
/GPIO43: J5.16, J6.46, JP6.2 (B), U1.54 (GPIO43/ADC3)
/GPIO44: J5.20, J6.42, JP5.2 (B), U1.55 (GPIO44/ADC4)
/GPIO45: J5.22, J6.40, JP7.1 (A), U1.56 (GPIO45/ADC5)
/GPIO46: J2.3, J5.26, J6.36, R8.1, U1.57 (GPIO46/ADC6)
/GPIO47: J2.4, J5.28, J6.34, R9.1, U1.58 (GPIO47/ADC7)
/I2C_PU: JP4.1 (A), R8.2, R9.2
/ID_PU: JP6.1 (A), R14.2
/LADDER: C22.1, JP5.1 (A), R10.2, SW1.1, SW2.1
/LED_DIN: JP7.2 (B), U4.2
/LED_DIN_5V: D2.4 (DIN), U4.4
/LED_DOUT: D2.2 (DOUT), J5.30
/QSPI_SS: SW3.1, U1.75 (~QSPI_SS)
/QWIIC_3V3: J2.2, JP3.2 (B)
/RUN: J4.12, TP3.1, U1.35 (RUN)
/SS_GATE: C20.2, Q1.1 (G), R7.1
/SWCLK: J4.16, TP1.1, U1.33 (SWCLK)
/SWDIO: J4.20, TP2.1, U1.34 (SWDIO)
/USB_DM: J1.A7 (D-), J1.B7 (D-), R4.1, U2.5
/USB_DM_MCU: R4.2, U1.66 (USB_DM)
/USB_DP: J1.A6 (D+), J1.B6 (D+), R3.1, U2.3
/USB_DP_MCU: R3.2, U1.67 (USB_DP)
/V5: C23.1, C24.1, D2.1 (VDD), J4.2, J4.4, J4.36, J4.40, J5.2, J5.4, J5.40, JP8.1 (A), Q1.3 (D), TP8.1, U4.5 (VCC)
/V5_FFC: J6.1, J6.2, JP8.2 (B)
/V5_IN: C18.1, C19.1, C20.1, D1.1 (K), Q1.2 (S), TP7.1, U3.1 (V_{IN}), U3.3 (CE)
/VBUS: F1.1, J1.A4 (VBUS), J1.A9 (VBUS), J1.B4 (VBUS), J1.B9 (VBUS), TP6.1
/VBUS_F: D1.2 (A), F1.2
/VREG_AVDD: C15.1, R1.2, U1.61 (VREG_AVDD)
/VREG_LX: L1.1, U1.63 (VREG_LX)
/XIN: C16.1, U1.30 (XIN), Y1.1
/XOUT: R2.1, U1.31 (XOUT)
/XTAL_OUT: C17.1, R2.2, Y1.3
